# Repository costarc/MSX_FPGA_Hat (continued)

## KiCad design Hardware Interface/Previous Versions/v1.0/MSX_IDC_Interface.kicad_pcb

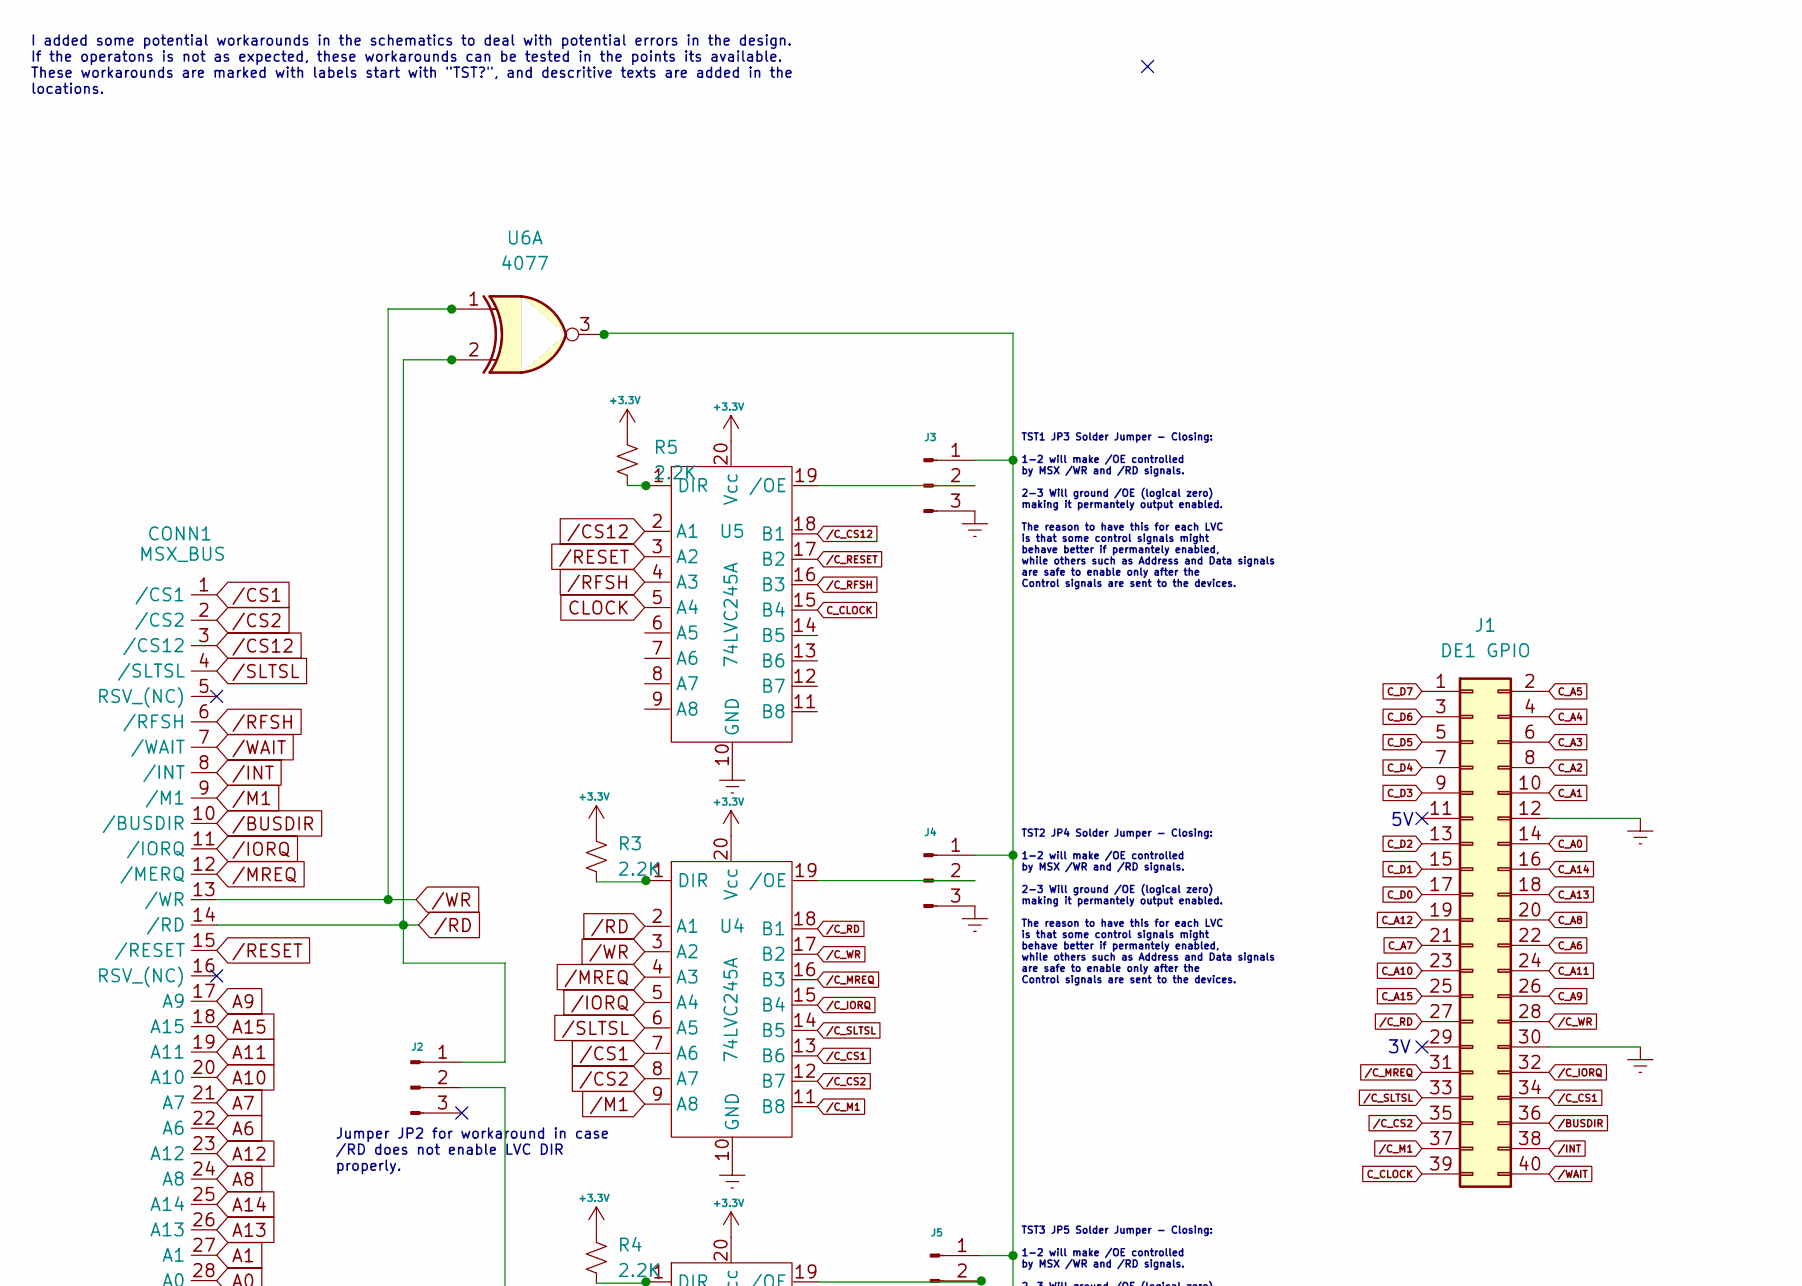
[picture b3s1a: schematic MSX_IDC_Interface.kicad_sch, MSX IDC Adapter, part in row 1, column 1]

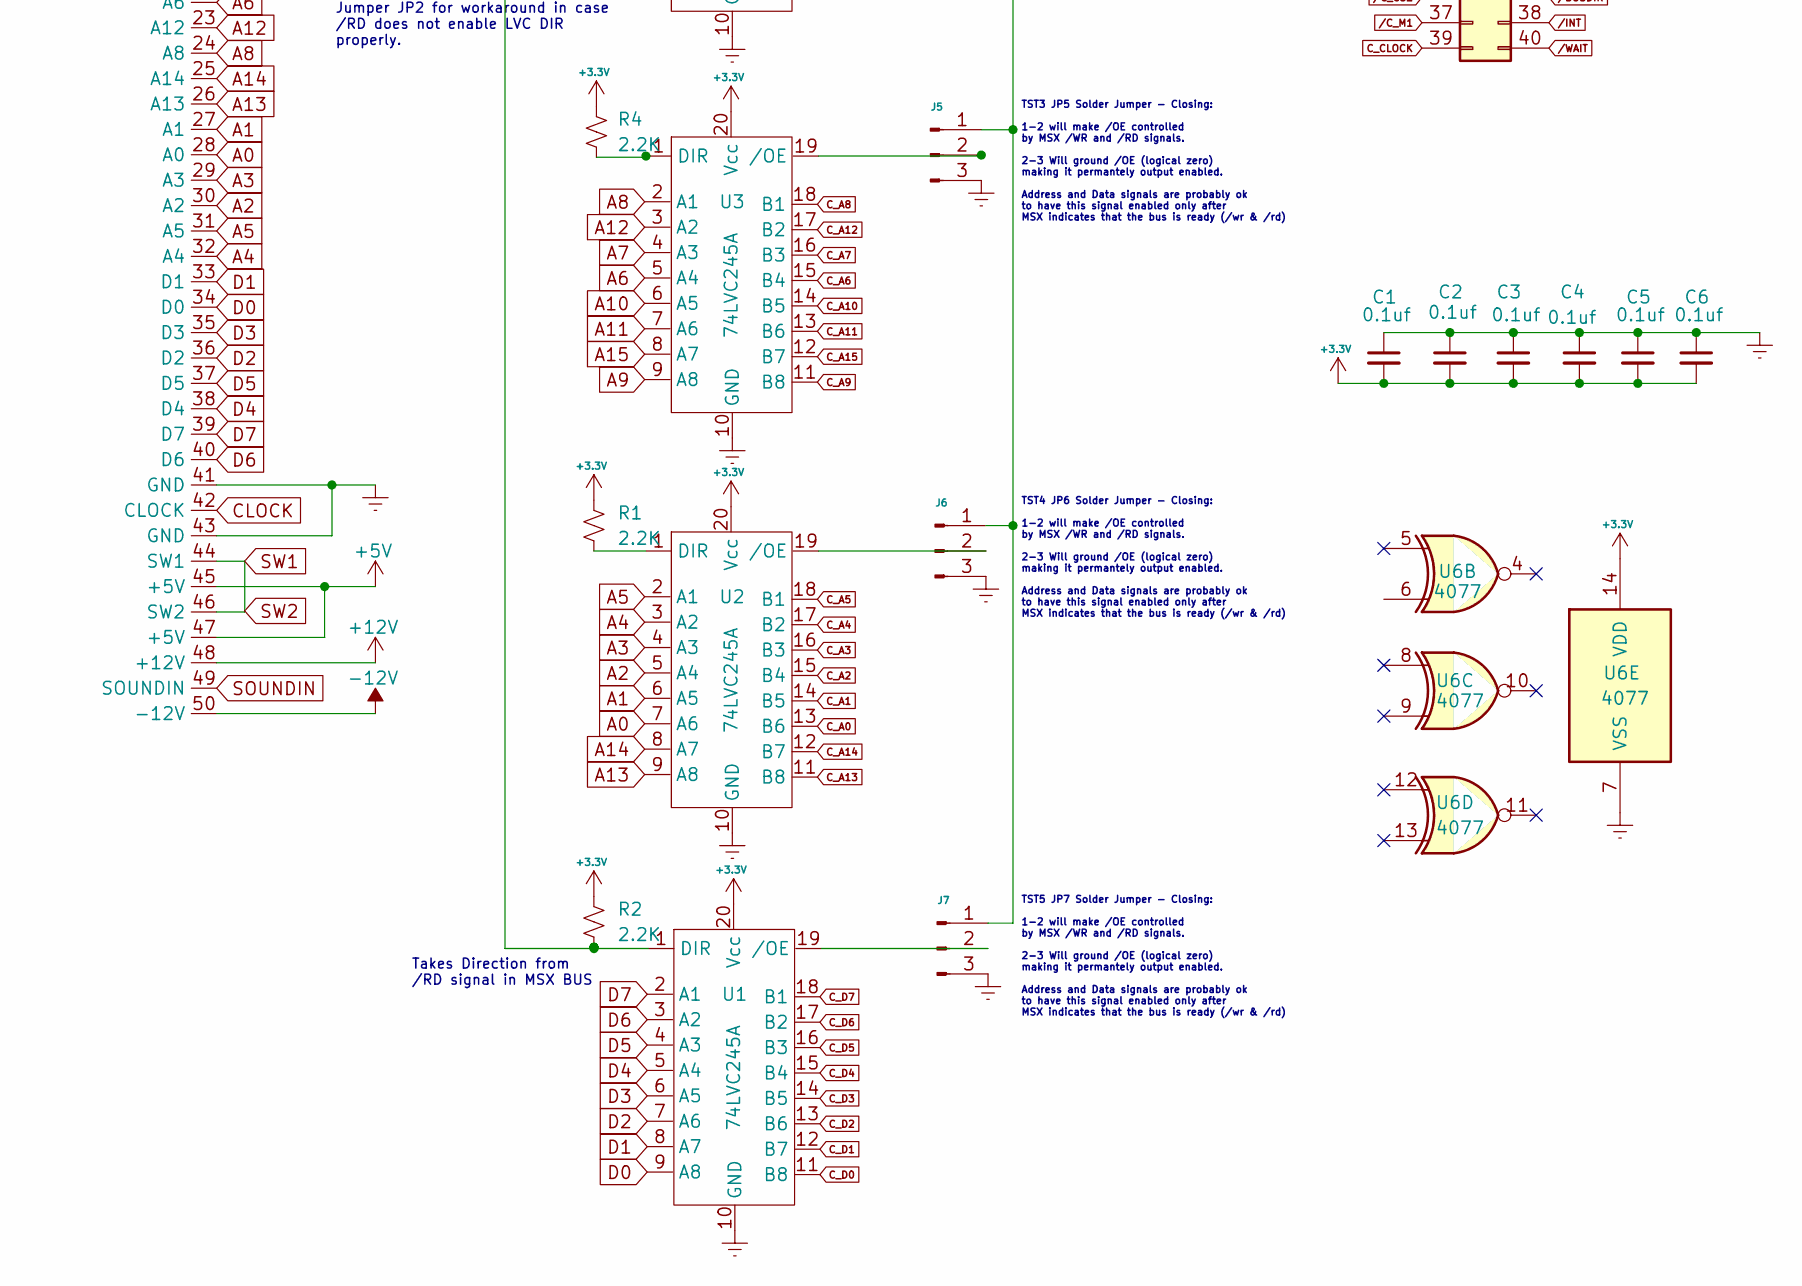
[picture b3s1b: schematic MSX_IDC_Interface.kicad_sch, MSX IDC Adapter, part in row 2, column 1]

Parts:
C1, C2, C3, C4, C5, C6: 0.1uf; C_Disc_D3.0mm_W1.6mm_P2.50mm
CONN1: MSX_BUS; MSX_CART
J1: DE1 GPIO; PinHeader_2x20_P2.54mm_Vertical
J2, J3, J4, J5, J6, J7: Conn_01x03_Male; PinHeader_1x03_P2.54mm_Vertical
R1, R2, R3, R4, R5: 2.2K; R_Axial_DIN0207_L6.3mm_D2.5mm_P7.62mm_Horizontal
U1, U2, U3, U4, U5: 74LVC245A; DIP-20_W7.62mm
U6: 4077; DIP-14_W7.62mm

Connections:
+3.3V: C1.2, C2.2, C3.2, C4.2, C5.2, C6.2, R1.1, R2.1, R3.1, R4.1, R5.1, U1.20 (Vcc), U2.20 (Vcc), U3.20 (Vcc), U4.20 (Vcc), U5.20 (Vcc), U6.14 (VDD)
+5V: CONN1.45 (+5V), CONN1.47 (+5V)
+12V: CONN1.48 (+12V)
-12V: CONN1.50 (-12V)
A0: CONN1.28 (A0), U2.7 (A6)
A1: CONN1.27 (A1), U2.6 (A5)
A2: CONN1.30 (A2), U2.5 (A4)
A3: CONN1.29 (A3), U2.4 (A3)
A4: CONN1.32 (A4), U2.3 (A2)
A5: CONN1.31 (A5), U2.2 (A1)
A6: CONN1.22 (A6), U3.5 (A4)
A7: CONN1.21 (A7), U3.4 (A3)
A8: CONN1.24 (A8), U3.2 (A1)
A9: CONN1.17 (A9), U3.9 (A8)
A10: CONN1.20 (A10), U3.6 (A5)
A11: CONN1.19 (A11), U3.7 (A6)
A12: CONN1.23 (A12), U3.3 (A2)
A13: CONN1.26 (A13), U2.9 (A8)
A14: CONN1.25 (A14), U2.8 (A7)
A15: CONN1.18 (A15), U3.8 (A7)
CLOCK: CONN1.42 (CLOCK), U5.5 (A4)
C_A0: J1.14, U2.13 (B6)
C_A1: J1.10, U2.14 (B5)
C_A2: J1.8, U2.15 (B4)
C_A3: J1.6, U2.16 (B3)
C_A4: J1.4, U2.17 (B2)
C_A5: J1.2, U2.18 (B1)
C_A6: J1.22, U3.15 (B4)
C_A7: J1.21, U3.16 (B3)
C_A8: J1.20, U3.18 (B1)
C_A9: J1.26, U3.11 (B8)
C_A10: J1.23, U3.14 (B5)
C_A11: J1.24, U3.13 (B6)
C_A12: J1.19, U3.17 (B2)
C_A13: J1.18, U2.11 (B8)
C_A14: J1.16, U2.12 (B7)
C_A15: J1.25, U3.12 (B7)
C_CLOCK: J1.39, U5.15 (B4)
C_D0: J1.17, U1.11 (B8)
C_D1: J1.15, U1.12 (B7)
C_D2: J1.13, U1.13 (B6)
C_D3: J1.9, U1.14 (B5)
C_D4: J1.7, U1.15 (B4)
C_D5: J1.5, U1.16 (B3)
C_D6: J1.3, U1.17 (B2)
C_D7: J1.1, U1.18 (B1)
D0: CONN1.34 (D0), U1.9 (A8)
D1: CONN1.33 (D1), U1.8 (A7)
D2: CONN1.36 (D2), U1.7 (A6)
D3: CONN1.35 (D3), U1.6 (A5)
D4: CONN1.38 (D4), U1.5 (A4)
D5: CONN1.37 (D5), U1.4 (A3)
D6: CONN1.40 (D6), U1.3 (A2)
D7: CONN1.39 (D7), U1.2 (A1)
GNDREF: C1.1, C2.1, C3.1, C4.1, C5.1, C6.1, CONN1.41 (GND), CONN1.43 (GND), J1.12, J1.30, J3.3, J4.3, J5.3, J6.3, J7.3, U1.10 (GND), U2.10 (GND), U3.10 (GND), U4.10 (GND), U5.10 (GND), U6.7 (VSS)
unnamed: J2.2, R2.2, U1.1 (DIR)
unnamed: J3.1, J4.1, J5.1, J6.1, J7.1, U6.3
unnamed: J3.2, U5.19 (/OE)
unnamed: J4.2, U4.19 (/OE)
unnamed: J5.2, U3.19 (/OE)
unnamed: J6.2, U2.19 (/OE)
unnamed: J7.2, U1.19 (/OE)
unnamed: R1.2, U2.1 (DIR)
unnamed: R3.2, U4.1 (DIR)
unnamed: R4.2, U3.1 (DIR)
unnamed: R5.2, U5.1 (DIR)
SOUNDIN: CONN1.49 (SOUNDIN)
SW1: CONN1.44 (SW1), CONN1.46 (SW2)
/BUSDIR: CONN1.10 (/BUSDIR), J1.36
/CS1: CONN1.1 (/CS1), U4.7 (A6)
/CS2: CONN1.2 (/CS2), U4.8 (A7)
/CS12: CONN1.3 (/CS12), U5.2 (A1)
/C_CS1: J1.34, U4.13 (B6)
/C_CS2: J1.35, U4.12 (B7)
/C_CS12: U5.18 (B1)
/C_IORQ: J1.32, U4.15 (B4)
/C_M1: J1.37, U4.11 (B8)
/C_MREQ: J1.31, U4.16 (B3)
/C_RD: J1.27, U4.18 (B1)
/C_RESET: U5.17 (B2)
/C_RFSH: U5.16 (B3)
/C_SLTSL: J1.33, U4.14 (B5)
/C_WR: J1.28, U4.17 (B2)
/INT: CONN1.8 (/INT), J1.38
/IORQ: CONN1.11 (/IORQ), U4.5 (A4)
/M1: CONN1.9 (/M1), U4.9 (A8)
/MREQ: CONN1.12 (/MERQ), U4.4 (A3)
/RD: CONN1.14 (/RD), J2.1, U4.2 (A1), U6.2
/RESET: CONN1.15 (/RESET), U5.3 (A2)
/RFSH: CONN1.6 (/RFSH), U5.4 (A3)
/SLTSL: CONN1.4 (/SLTSL), U4.6 (A5)
/WAIT: CONN1.7 (/WAIT), J1.40
/WR: CONN1.13 (/WR), U4.3 (A2), U6.1

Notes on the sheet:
I added some potential workarounds in the schematics to deal with potential errors in the design. If the operatons is not as expected, these workarounds can be tested in the points its available. These workarounds are marked with labels start with "TST?", and descritive texts are added in the locat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
TST4 JP6 Solder Jumper - Closing: 1-2 will make /OE controlled by MSX /WR and /RD signals. 2-3 Will ground /OE (logical zero) making it permantely output enabled. Address and Data signals are probably ok to have this signal enabled only after MSX indicates that the bus is ready (/wr & /rd)
TST1 JP3 Solder Jumper - Closing: 1-2 will make /OE controlled by MSX /WR and /RD signals. 2-3 Will ground /OE (logical zero) making it permantely output enabled. The reason to have this for each LVC is that some control signals might behave better if permantely enabled, while others such as Addres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
TST3 JP5 Solder Jumper - Closing: 1-2 will make /OE controlled by MSX /WR and /RD signals. 2-3 Will ground /OE (logical zero) making it permantely output enabled. Address and Data signals are probably ok to have this signal enabled only after MSX indicates that the bus is ready (/wr & /rd)
TST2 JP4 Solder Jumper - Closing: 1-2 will make /OE controlled by MSX /WR and /RD signals. 2-3 Will ground /OE (logical zero) making it permantely output enabled. The reason to have this for each LVC is that some control signals might behave better if permantely enabled, while others such as Addres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
Jumper JP2 for workaround in case /RD does not enable LVC DIR properly.
Takes Direction from /RD signal in MSX BUS
TST5 JP7 Solder Jumper - Closing: 1-2 will make /OE controlled by MSX /WR and /RD signals. 2-3 Will ground /OE (logical zero) making it permantely output enabled. Address and Data signals are probably ok to have this signal enabled only after MSX indicates that the bus is ready (/wr & /rd)

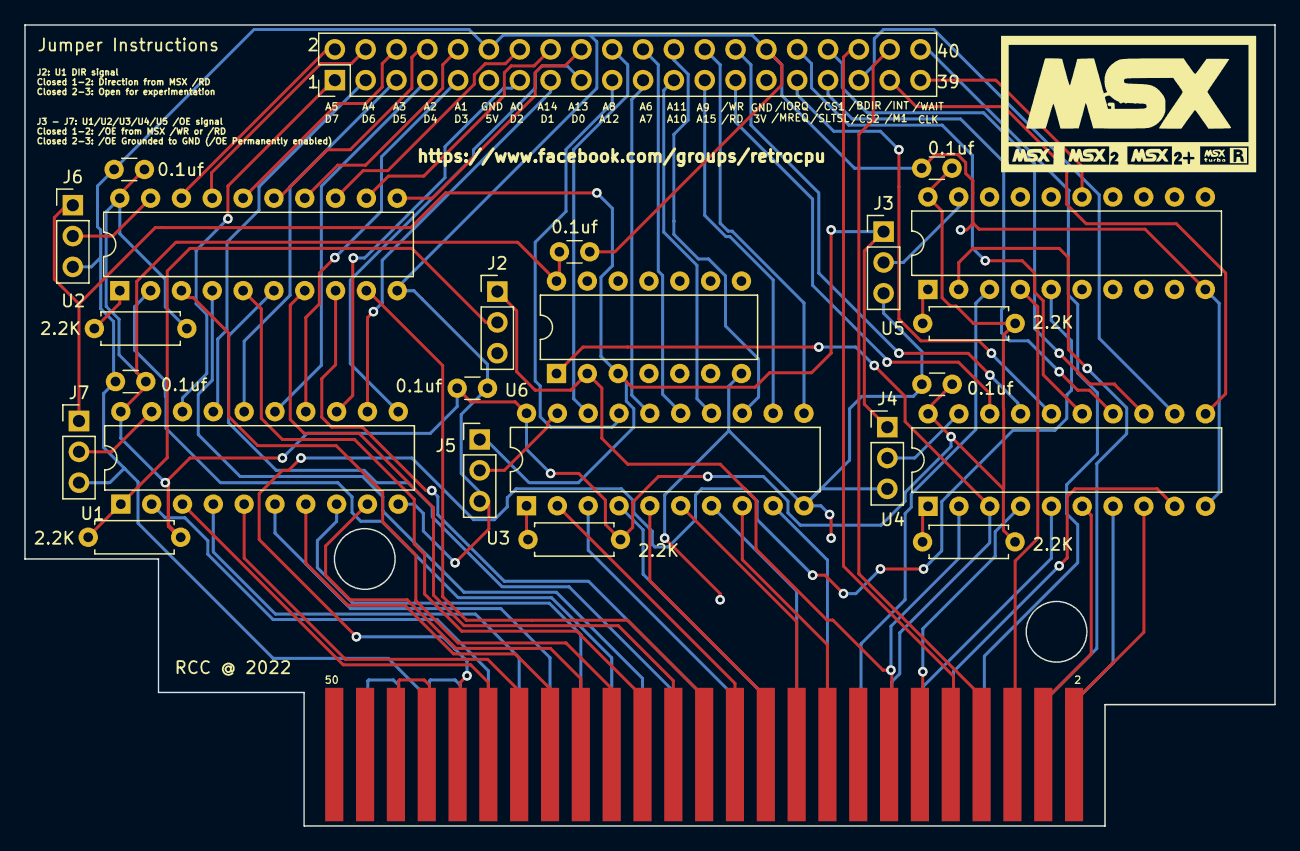
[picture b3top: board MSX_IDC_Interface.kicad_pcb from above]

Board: 2 copper layers, 103.0 x 66.0 mm, 26 parts (1 on the bottom side), 87 nets.

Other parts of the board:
CD4077 / XNOR Truth Table: LOGO

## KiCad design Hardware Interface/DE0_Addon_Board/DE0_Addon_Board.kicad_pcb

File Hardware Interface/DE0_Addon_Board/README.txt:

This is a SRAM Addon for Terasic DE0 development board.

This Add-on is a 8 bits data bus only, 2 x 256KB banks (the DE1 and other models has the same SRAM, but in a 16 bus width).

LB_n and UB_n enable the two banks (only one should be enabled at any time), because both banks shares the same GPIO pins in the DE0 board.

The Raspberry Pi GPIO header should only be used when CE_n is HIGH (1), which disables teh SRAM and keeps the bus free for the Raspberry Pi.

Change History
--------------

Rev 2
- Changed footprint for the capacitors from 0402 to 0603 size

Rev 1
- Changed the add-on PIN Header from standard DE0 to Raspberry Pi layout to support Raspberry Pi as an connected device

Rev 0
- Initial version

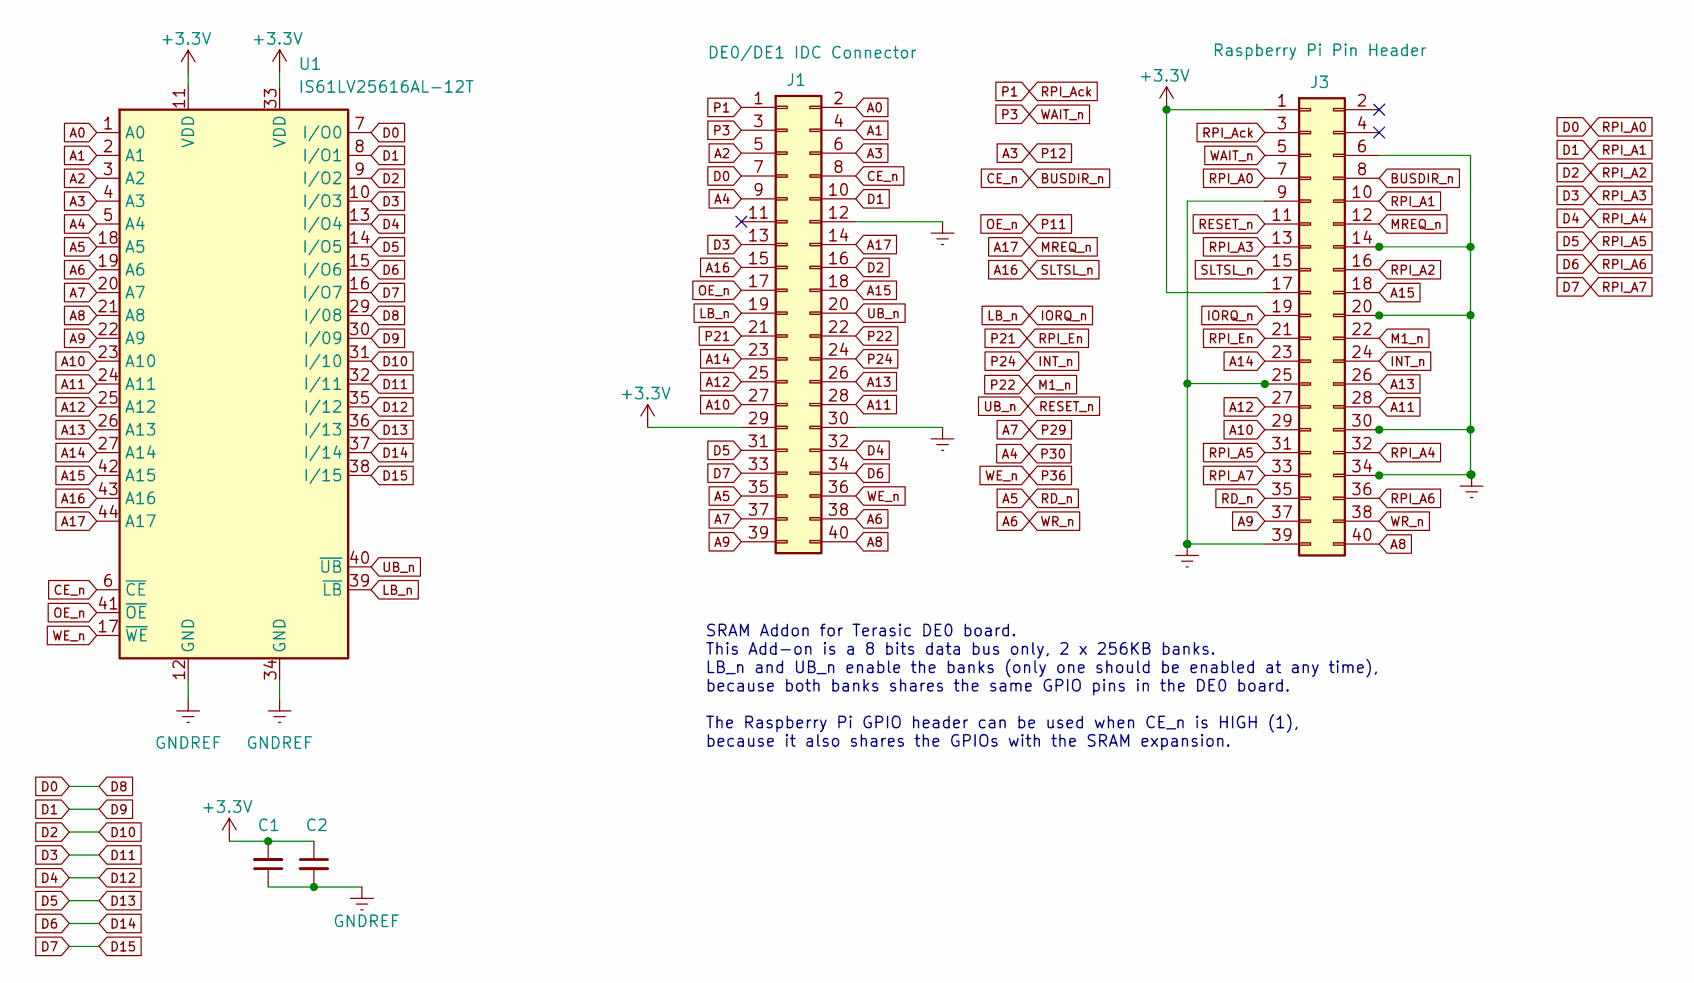
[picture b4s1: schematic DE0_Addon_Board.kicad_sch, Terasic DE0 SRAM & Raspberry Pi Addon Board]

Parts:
C1, C2: C_Small; C_0603_1608Metric_Pad1.08x0.95mm_HandSolder
J1: DE0/DE1 IDC Connector; PinSocket_2x20_P2.54mm_Vertical
J3: Raspberry Pi Pin Header; PinHeader_2x20_P2.54mm_Vertical
U1: IS61LV25616AL-12T; SOP80P1176X120-44N

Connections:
+3.3V: C1.2, C2.1, J1.29, J3.1, J3.17, U1.11 (VDD), U1.33 (VDD)
A0: J1.2, U1.1 (A0)
A1: J1.4, U1.2 (A1)
A2: J1.5, U1.3 (A2)
A3: J1.6, U1.4 (A3)
A4: J1.9, U1.5 (A4)
A5: J1.35, J3.35, U1.18 (A5)
A6: J1.38, J3.38, U1.19 (A6)
A7: J1.37, U1.20 (A7)
A8: J1.40, J3.40, U1.21 (A8)
A9: J1.39, J3.37, U1.22 (A9)
A10: J1.27, J3.29, U1.23 (A10)
A11: J1.28, J3.28, U1.24 (A11)
A12: J1.25, J3.27, U1.25 (A12)
A13: J1.26, J3.26, U1.26 (A13)
A14: J1.23, J3.23, U1.27 (A14)
A15: J1.18, J3.18, U1.42 (A15)
A16: J1.15, J3.15, U1.43 (A16)
A17: J1.14, J3.12, U1.44 (A17)
BUSDIR_n: J1.8, J3.8, U1.6 (~CE)
D0: J1.7, J3.7, U1.7 (I/O0), U1.29 (I/08)
D1: J1.10, J3.10, U1.8 (I/O1), U1.30 (I/09)
D10: J1.16, J3.16, U1.9 (I/O2), U1.31 (I/10)
D11: J1.13, J3.13, U1.10 (I/O3), U1.32 (I/11)
D12: J1.32, J3.32, U1.13 (I/O4), U1.35 (I/12)
D13: J1.31, J3.31, U1.14 (I/O5), U1.36 (I/13)
D14: J1.34, J3.36, U1.15 (I/O6), U1.37 (I/14)
D15: J1.33, J3.33, U1.16 (I/O7), U1.38 (I/15)
GNDREF: C1.1, C2.2, J1.12, J1.30, J3.6, J3.9, J3.14, J3.20, J3.25, J3.30, J3.34, J3.39, U1.12 (GND), U1.34 (GND)
INT_n: J1.24, J3.24
IORQ_n: J1.19, J3.19, U1.39 (~LB)
M1_n: J1.22, J3.22
OE_n: J1.17, U1.41 (~OE)
P1: J1.1, J3.3
P3: J1.3, J3.5
P21: J1.21, J3.21
P36: J1.36, U1.17 (~WE)
RESET_n: J1.20, J3.11, U1.40 (~UB)

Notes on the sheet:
SRAM Addon for Terasic DE0 board. This Add-on is a 8 bits data bus only, 2 x 256KB banks. LB_n and UB_n enable the banks (only one should be enabled at any time), because both banks shares the same GPIO pins in the DE0 board. The Raspberry Pi GPIO header can be used when CE_n is HIGH (1), because i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

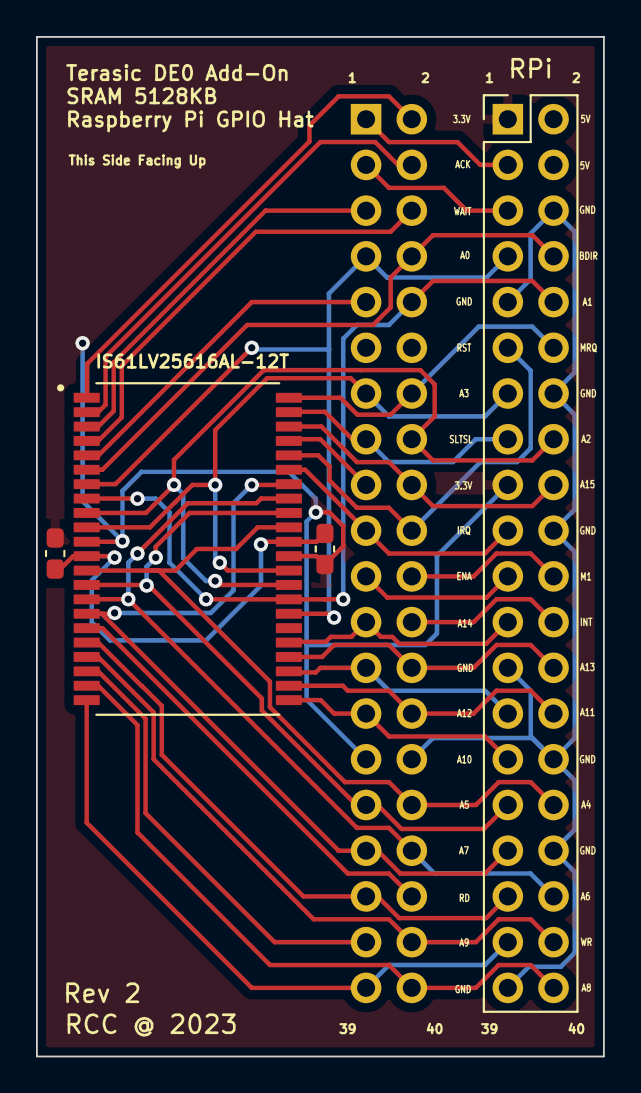
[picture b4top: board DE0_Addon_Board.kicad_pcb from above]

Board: 2 copper layers, 31.5 x 56.6 mm, 5 parts (1 on the bottom side), 38 nets.

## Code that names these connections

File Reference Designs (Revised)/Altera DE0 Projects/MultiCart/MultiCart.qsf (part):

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set_location_assignment PIN_B12 -to CLOCK_50_2
# --
set_location_assignment PIN_AB11 -to MSXCLK
set_location_assignment PIN_AA20 -to RESET_n
set_location_assignment PIN_AA11 -to CS1_n
set_location_assignment PIN_AB20 -to RD_n
set_location_assignment PIN_AA19 -to WAIT_n
set_location_assignment PIN_AB19 -to CS2_n
set_location_assignment PIN_AB18 -to SOUND
set_location_assignment PIN_AA18 -to AUDIO
set_location_assignment PIN_AA17 -to M1_n
set_location_assignment PIN_AB17 -to U4_OE_n
set_location_assignment PIN_Y17 -to MREQ_n
set_location_assignment PIN_W17 -to SLTSL_n
set_location_assignment PIN_U15 -to WR_n
set_location_assignment PIN_T15 -to IORQ_n
set_location_assignment PIN_W15 -to A4_12
set_location_assignment PIN_V15 -to U3_OE_n
set_location_assignment PIN_R16 -to BUSDIR_n
set_location_assignment PIN_AB9 -to A5_13
set_location_assignment PIN_T16 -to INT_n
set_location_assignment PIN_AA9 -to A2_10
set_location_assignment PIN_AA7 -to A3_11
set_location_assignment PIN_AB7 -to U2_OE_n
set_location_assignment PIN_T14 -to A1_9
set_location_assignment PIN_R14 -to A0_8
set_location_assignment PIN_U12 -to A7_15
set_location_assignment PIN_T12 -to A6_14
set_location_assignment PIN_R11 -to D[6]
set_location_assignment PIN_R12 -to D[7]
set_location_assignment PIN_U10 -to D[4]
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
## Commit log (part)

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2022-11-13 Changed the schematic to use a NAND port via transitors - to remove the 74LS00. Started routing the PCB
2022-11-13 Added both NAD options to same schematic -with 74LS00 and other option with tranistors
2022-11-13 Safe guard commit - progressing with routing
2022-11-14 Finished routing. Rules chekc not done yet
2022-11-14 Resolvig clearance issues - wip
2022-11-15 Changed NAND gate for XNOR gate (bug); Completed routing
2022-11-15 Resistors changed to 2.2k and routing completed
2022-11-15 Added silkscreen to pcb
2022-11-15 Version 1.0 with fabrication files
2022-11-16 Repositioned background silk and removed unwanted G** in the galaga silk. Continue being Verison 1.0
2022-11-16 Generated updated Gerbers for verison 1.0
2022-12-13 Fixed missing 3v input
2022-12-13 Fixed missing 3v input & minor cosmetic change
2022-12-14 Changed directory structure; Added Altera DE1 qsf file (oin assignments to match MSX Bus
2022-12-14 added .gitignore
2022-12-14 deleted .DS_Store
2022-12-14 Renamed the project from MSX IDC Interface to MSX DE1 hat
2022-12-14 Small change to silk text
2022-12-14 Rev 1.1. Added pull ups for /OE; Changed Pull Ups to 10K; Changed silk screen
2022-12-14 New branch - Commit to have a rollback point
2022-12-14 Changed LVC245 DIR signal - to be enabled via MSX /RD
2022-12-15 Merged changes to drive LCV245 DIR from MSX /RD
2022-12-15 Added Gerbers for V1.1
2022-12-15 First Quartus build
2022-12-16 DE1 parcially readign MSX BUS
2022-12-16 Updated PCB Rev 1.1 with IDC connector in right position
2023-01-02 some backups deleted
2023-01-06 reseted to previous commit - to discard any jumper addition to support rpi
2023-01-06 Abandoned the idea of making this design support both DE1 & RPi
2023-01-06 Merged manually firmaware files from Rev1.0
2023-01-07 Added working firmware / vhdl. Updated schematic and pcb to rmove not needed components
2023-01-08 Updated firmware and schematic following tests in Rev1.0 branch
2023-01-08 Starting routing of reivsed pcb
2023-01-09 Routing new pcb for v1.1
2023-01-09 Fabricatin files added for the PCB v1.1
2023-01-09 Both QSF files for GPIO mappings (Rev1.0 and Rev 1.1)
2023-01-10 Changed register in I/O to process
2023-01-10 Adding mapper vhdl components
2023-01-12 EPCS4 Programing (Non-Volatile Programming)
    EPCS4 Programing (Non-Volatile Programming)
2023-01-12 Generated jic file to program EPCS4
2023-01-12 Added DE0 Project directory
2023-01-12 Added the logic devices from indivudual 74hcnnn components
2023-01-13 mapper components added but not working - locks the computer
2023-01-16 Renamed to MSX FPGA Hat
2023-01-17 Added Gerber files
2023-01-17 Compatibel with DE0 & DE1
2023-01-17 Renamed kicad files to MSX FPGA Hat
2023-01-17 Added project andpin mapping for DE0
2023-01-17 cleaned up building files
2023-01-17 Compiliatin working after rebase
2023-01-17 Fixed a type, cleaned up. Working multicart emulation
2023-01-21 MegarOM ASCII16 Functional
2023-01-21 Re-strcutured FPGA directories
2023-01-21 MegaROM Mappers added - ASCI16 and KONAMI8
2023-01-22 Restarting RAM Mapper development
2023-01-22 Mapper implementaation: registers implemented, MSX recognize more memory but bank switch is not working
2023-01-22 Developing the MSXDOS2/Nextor reference design
2023-01-22 Fixed some erros in FL_CE_N and other related SD/ROM signals
2023-01-23 DOS boots, but cannot find SD Cards
2023-01-23 RAM pokes work, but reads present delayed data
2023-01-23 RAM can be used, but mapper is not working
2023-01-24 Removed component SRAM, moved codigo to top component
2023-01-24 Memory Mapper 512K working - tested on Canon V-8 12KB RAM
2023-01-24 Updated schmeatic and PCB to Rev 1.2
2023-01-24 Added gerbers in ZIP format
2023-01-25 Adding SDCard reference design
2023-01-26 Tweaked with the enable signals and made more clean and simple
2023-01-27 MSXDOS boots into DiSK BASIC, ROM Mapper working. SDCARD / SPIO not working
2023-01-29 Added project for Add-On board SRAM 512KB for DE0
2023-01-29 Added 2nd IDC connector in paralell with the SRAM
2023-01-30 SD Card access fails, but now tries to read SD2 and fails if card removed
2023-01-30 It freaking worksgit add .git add . With 2nd SD Card only
2023-01-31 Success! Booting Nextor from SD CARD 1 and/or 2
2023-01-31 Reverted the interface schema to v1.1, as it's verified that U1 does not need to be driven by its own 7 separate pin. BUSDIR in the FPGA will continue driving both MSX BUSDIR and U1 DIR pin
2023-01-31 Reverted the interface schema to v1.1, as it's verified that U1 does not need to be driven by its own 7 separate pin. BUSDIR in the FPGA will continue driving both MSX BUSDIR and U1 DIR pin. Added re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
2023-01-31 Moving to version 1.2 as it's clear that the OD pin in the U1 is not being driven correctly and need a separate pin for this purpose. V1.2 has this change implemented
2023-01-31 all versions available to facilitate debugging and working with the old revisons wired up for fixes
2023-01-31 Added proper readme
2023-02-01 Added pin U1OE_n to controll /OE in U1; Update design files with this change
2023-02-02 Changing daughter board to support raspberry pin connector
2023-02-02 Addon-board changed to support Raspberry Pi in the GPIO connector
2023-02-04 tweaked busdir/U1 /oe. booting everythign on Zemmix
2023-02-04 Mapper passed TESTRAM tests; With slot expansor implemented
2023-02-04 MegaRAM detected for 8KB only
2023-02-06 MegaRAM working without expanded slots.
2023-02-06 SDMapper added. Unstable on Canon V-8, although works well with Zemmix
2023-02-12 Adding REference Designs for DE0
2023-02-16 Changed footprint of SRAM decoupling capacitors to SMD 0603; Updated SRAM Addon for Rev.2
2023-02-17 Updated footprint for the pcb to make insertion into slot easier
2023-02-18 Added blockrom cartridge emulator - working in DE1
2023-02-18 Galaga booting on DE0 using BlockROM
2023-02-19 Working with the mapper for DE0 & DE1; it stopped workig with the new PCB v1.1
2023-02-20 MegaRM core functional with DE0 SRAM Addon
2023-02-20 Mapper 512KB functional with DE0 SRAM Addon
2023-02-21 Updated Add-On with silk in addresses for RPI
2023-02-21 Updated schema and pcb with some cool silk and instructions
2023-02-21 Added option to power the interface by MSX
2023-02-21 Added pull-ups for int,wait,busdir (optional)
2023-02-21 small fix to the silk
2023-02-28 Updated edge connector to meet MSX specifications
2023-03-01 Finalized v1.3; new silk; new routing for soundin & rfsh; changed jumper J1
2023-03-14 Updated rom_to_vhd.py
2023-03-14 SDCard access working using GPIO1 SDCARD 16GB. Does not recognize card in DE1 slot
2023-03-14 Fixed bug in pin assignment that was breaking SDCard functionality in DE1
2023-03-14 added pdf with SDCARD various pinout identificatins
2023-03-14 updated .gitignore
2023-03-14 programming file generated for DE1
2023-03-17 Updated footprint for cart with little move in hole places to better fit patola/brazil case
2023-05-14 Added pull-up with 4 x resistor arrays; added reset button
2023-05-14 Created dirctory v1.3 prior to merging new version 1.4
2023-05-15 Added Gerber for v1.4
2023-05-29 Added fabrication instructions
2023-11-09 V 1.5
2023-12-08 Changed SPI clock to PLL
2023-12-10 New DE1ROMs layout with SDMApper on address 0x0000
2023-12-11 v1.6
2023-12-11 v1.6 candidate & v1.4 added for backup
2023-12-18 Version 2.0
2023-12-18 Removed temporary work folder
2023-12-18 Added Wondertang project - incluid MSX Multi FPGA mod
2023-12-18 Moved al previous versions to a separete folder
2024-01-23 Rewriting SDMAPPER
2024-02-03 ev 2.0
2024-02-03 Rev 1.5
2024-02-03 v2.0 has a bug - added a info in the schematic
2024-02-03 V2.01
2024-02-06 Master is currentl under development and tests for v2.0
2024-04-19 Create LICENSE
2024-04-19 Added LICENSE files
2024-07-22 changed fabrication instructions - edge angle now is recommended to 45 degrees
